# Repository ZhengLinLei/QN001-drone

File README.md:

<h1 align="center">QingNiao Drone Model 001</h1>
<br>
<br>

<p align="center">
  <i>Drone prototype to test Oroneta System</i>
</p>

<p align="center">
  <a href="./CONTRIBUTING.md">Contributing</a>
  ·
  <a href="https://github.com/ZhengLinLei/QN001-drone/issues">Issues</a>
</p>

<p align="center">
  &nbsp;
  
</p>

<hr>

## Table of Contents

- [Introduction](#introduction)
- [Features](#features)
- [User Guide](#user-guide)
- [Installation](#installation)

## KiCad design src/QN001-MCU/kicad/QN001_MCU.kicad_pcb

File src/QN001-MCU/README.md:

# Project supported for two protocols: QN001-MCU

1. ADMP (Private protocol)
2. MAVLink (Public protocol)

## User Guide

Flash the best firmware for your project. Both protocols are supported.

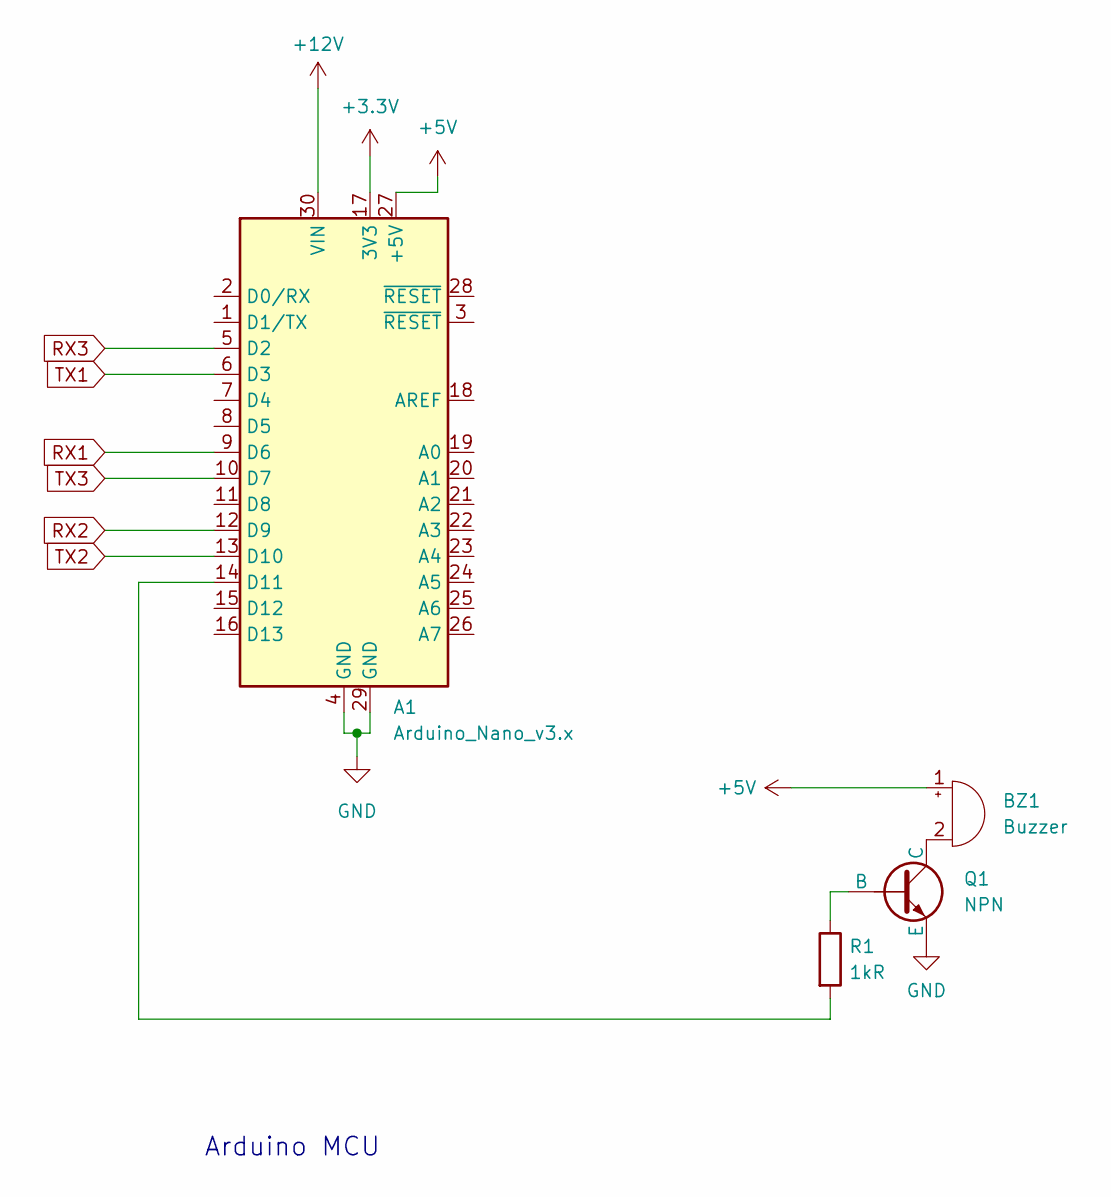
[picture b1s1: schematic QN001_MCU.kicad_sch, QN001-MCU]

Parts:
A1: Arduino_Nano_v3.x; Arduino_Nano
BZ1: Buzzer; Buzzer_15x7.5RM7.6
Q1: NPN; TO-92_Inline
R1: 1kR; R_Axial_DIN0414_L11.9mm_D4.5mm_P20.32mm_Horizontal

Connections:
+3.3V: A1.17 (3V3)
+5V: A1.27 (+5V), BZ1.1 (-)
+12V: A1.30 (VIN)
GND: A1.4 (GND), A1.29 (GND), Q1.3 (E)
unnamed: A1.14 (D11), R1.2
unnamed: BZ1.2 (+), Q1.1 (C)
unnamed: Q1.2 (B), R1.1
RX1: A1.9 (D6)
RX2: A1.12 (D9)
RX3: A1.5 (D2)
TX1: A1.6 (D3)
TX2: A1.13 (D10)
TX3: A1.10 (D7)

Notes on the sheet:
Arduino MCU

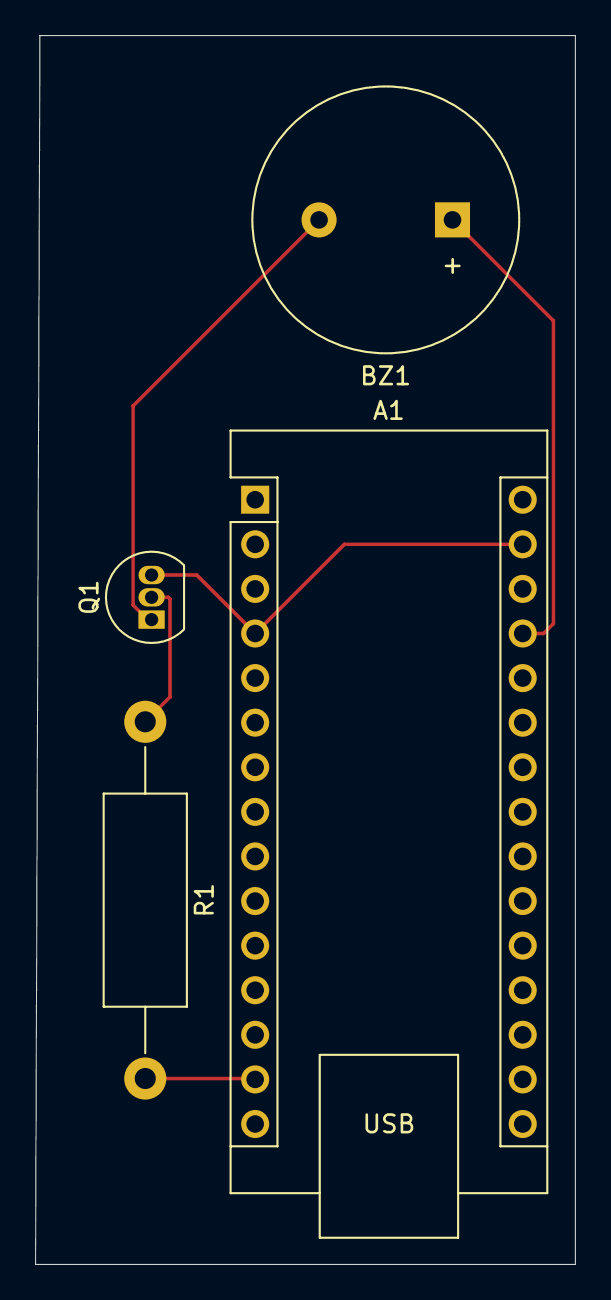
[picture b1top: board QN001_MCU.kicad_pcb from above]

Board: 2 copper layers, 30.8 x 70.0 mm, 4 parts (0 on the bottom side), 5 nets.

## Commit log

2024-03-26 Init ESP32CAM
2024-04-10 Drone update
2024-04-15 tmp2
2024-04-16 Added Wifi control and extras
2024-04-16 Added Wifi and extras, including esp_camera (#3)
    * tmp
    * tmp2
    * Added Wifi control and extras
2024-04-16 Added testing host
2024-04-17 HTTP fix
2024-04-17 Feature task wifi (#4)
    * tmp
    * tmp2
    * Added Wifi control and extras
    * Added testing host
    * HTTP fix
2024-04-17 Camera changes tmp
2024-04-20 Added server upload and test server
2024-04-20 Feature task wifi with server(#5)
    * tmp
    * tmp2
    * Added Wifi control and extras
    * Added testing host
    * HTTP fix
    * Added server upload and test server
2024-04-20 Kicad
2024-04-22 Added ixing and example
2024-05-14 Added Serial code
2024-05-15 Added Serial update

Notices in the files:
README.md:
License: MIT
